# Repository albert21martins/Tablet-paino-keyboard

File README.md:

# Tablet-paino-keyboard
Bluetooth Low Energy 1- button Keyboard controller for Tablets.

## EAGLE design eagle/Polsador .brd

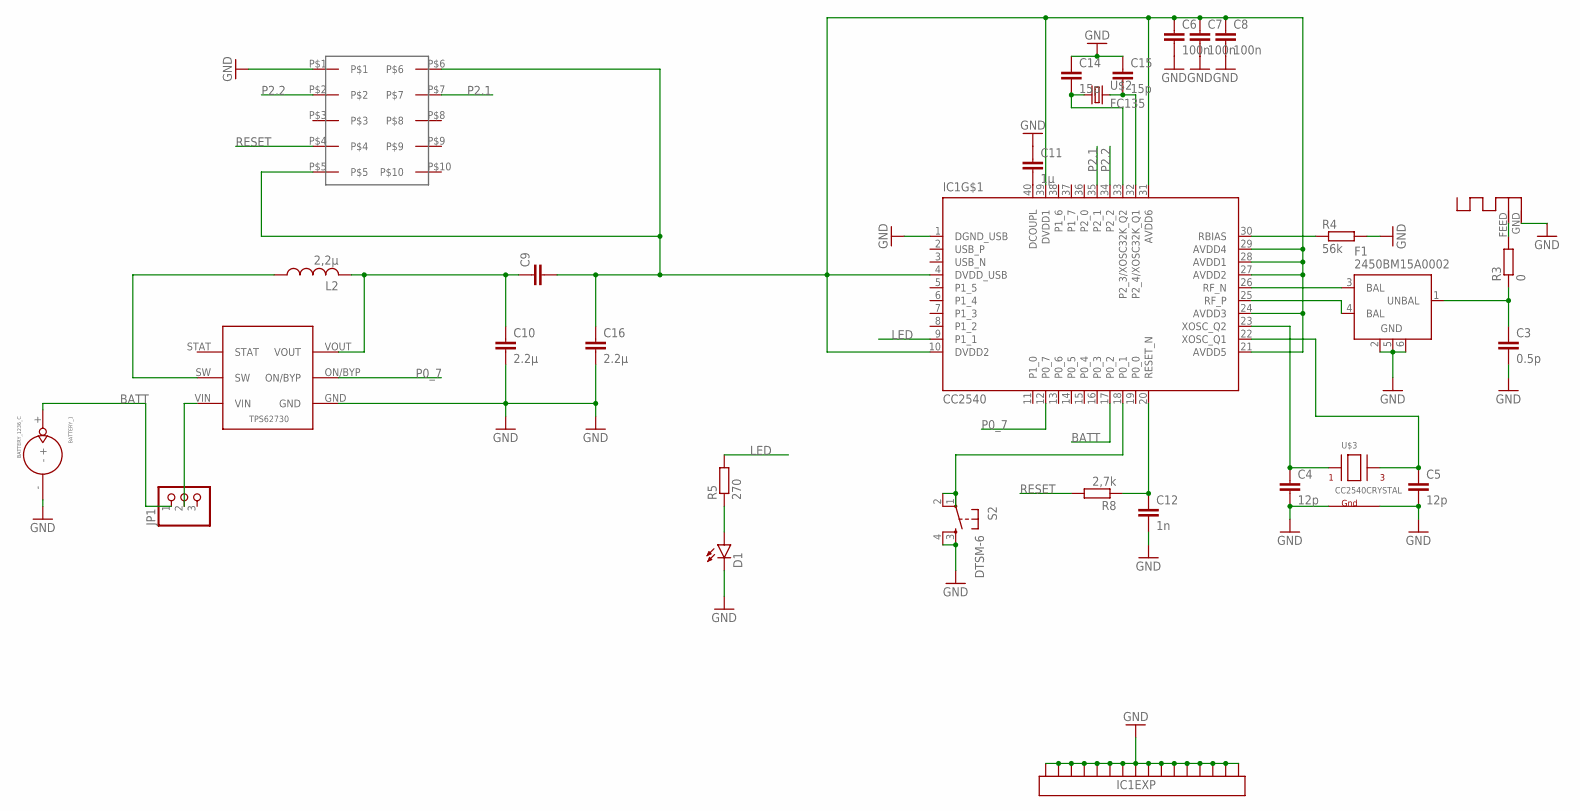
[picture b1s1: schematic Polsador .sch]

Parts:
ANT1: ANTENNA; RN-ANT
BATTERY_1: BATTERY_1236_C
C3: 0.5p; C0402K
C4, C5: 12p; C0402K
C6, C7, C8: 100n; C0402K
C9: C-EUC0402; C0402
C10, C16: 2.2µ; C0402K
C11: 1µ; C0402K
C12: 1n; C0402K
C14, C15: 15p; C0402K
D1: LED0603; LED-0603
F1: 2450BM15A0002
IC1: CC2540; QFN40-6X6
JP1: PINHD-1X3; 1X03
L2: 2,2µ; L2012C
R3: 0; R0402
R4: 56k; R0402
R5: 270; R0402
R8: 2,7k; R0402
S2: DTSM-6
U$1: DEBUG
U$2: FC135
U$3: CC2540CRYSTAL
U$4: TPS62730

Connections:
BATT: BATTERY_1.+, IC1.17 (P0_2), JP1.1
GND: ANT1.GND, BATTERY_1.-, C3.2, C4.2, C5.2, C6.2, C7.2, C8.2, C10.2, C11.1, C12.2, C14.1, C15.1, C16.2, D1.C, F1.2 (GND), F1.5 (GND), F1.6 (GND), IC1.1 (DGND_USB), IC1.EXP@1 (EXP16), IC1.EXP@2 (EXP16), IC1.EXP@3 (EXP16), IC1.EXP@4 (EXP16), IC1.EXP@5 (EXP16), IC1.EXP@6 (EXP16), IC1.EXP@7 (EXP16), IC1.EXP@8 (EXP16), IC1.EXP@9 (EXP16), IC1.EXP@10 (EXP16), IC1.EXP@11 (EXP16), IC1.EXP@12 (EXP16), IC1.EXP@13 (EXP16), IC1.EXP@14 (EXP16), IC1.EXP@15 (EXP16), IC1.EXP@16 (EXP16), R4.2, S2.3, S2.4, U$1.P$1, U$3.2 (G1), U$3.4 (G2), U$4.GND
LED: IC1.9 (P1_1), R5.2
unnamed: C14.2, IC1.33 (P2_3/XOSC32K_Q2), U$2.1
unnamed: C15.2, IC1.32 (P2_4/XOSC32K_Q1), U$2.2
unnamed: IC1.18 (P0_1), S2.1, S2.2
unnamed: L2.1, U$4.SW
unnamed: C9.1, C10.1, L2.2, U$4.VOUT
unnamed: C4.1, IC1.23 (XOSC_Q2), U$3.1 (X1)
unnamed: F1.3 (BAL), IC1.26 (RF_N)
unnamed: F1.4 (BAL), IC1.25 (RF_P)
unnamed: C3.1, F1.1 (UNBAL), R3.1
unnamed: ANT1.FEED, R3.2
unnamed: C5.1, IC1.22 (XOSC_Q1), U$3.3 (X2)
unnamed: IC1.30 (RBIAS), R4.1
unnamed: C11.2, IC1.40 (DCOUPL)
unnamed: C12.1, IC1.20 (RESET_N), R8.1
unnamed: C6.1, C7.1, C8.1, C9.2, C16.1, IC1.4 (DVDD_USB), IC1.10 (DVDD2), IC1.21 (AVDD5), IC1.24 (AVDD3), IC1.27 (AVDD2), IC1.28 (AVDD1), IC1.29 (AVDD4), IC1.31 (AVDD6), IC1.39 (DVDD1), U$1.P$5, U$1.P$6
unnamed: JP1.2, U$4.VIN
unnamed: D1.A, R5.1
P0_7: IC1.12 (P0_7), U$4.ON/BYP
P2.1: IC1.35 (P2_1), U$1.P$7
P2.2: IC1.34 (P2_2), U$1.P$2
RESET: R8.2, U$1.P$4

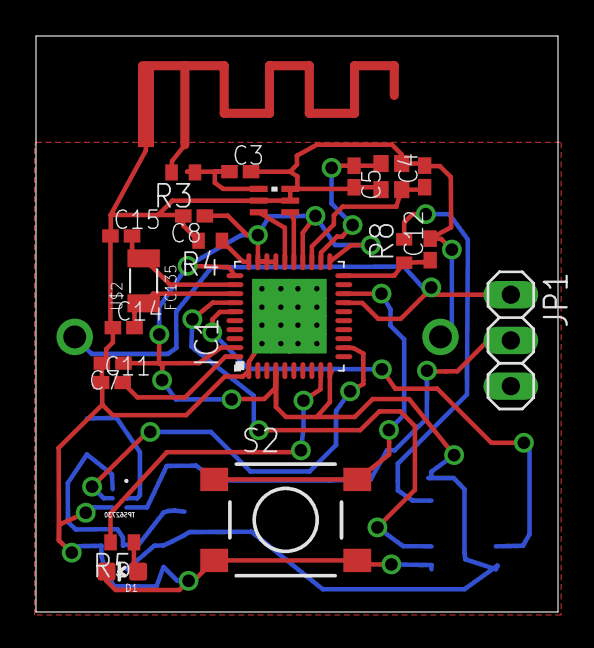
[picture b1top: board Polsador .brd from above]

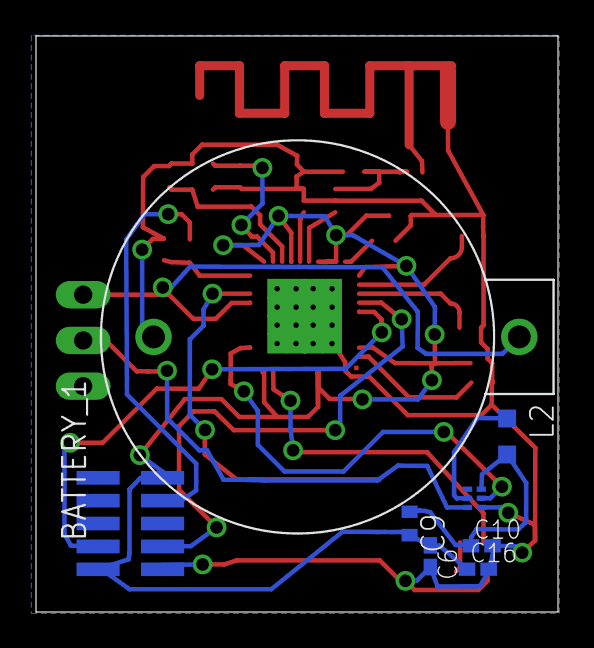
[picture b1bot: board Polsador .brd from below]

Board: 2 copper layers, 29.0 x 32.0 mm, 29 parts (8 on the bottom side), 24 nets.

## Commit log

2015-11-07 1button table keyboard

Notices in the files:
parts and their libraries:
SparkFun-LED: Licensing: Creative Commons ShareAlike 4.0 International - https://creativecommons.org/licenses/by-sa/4.0
